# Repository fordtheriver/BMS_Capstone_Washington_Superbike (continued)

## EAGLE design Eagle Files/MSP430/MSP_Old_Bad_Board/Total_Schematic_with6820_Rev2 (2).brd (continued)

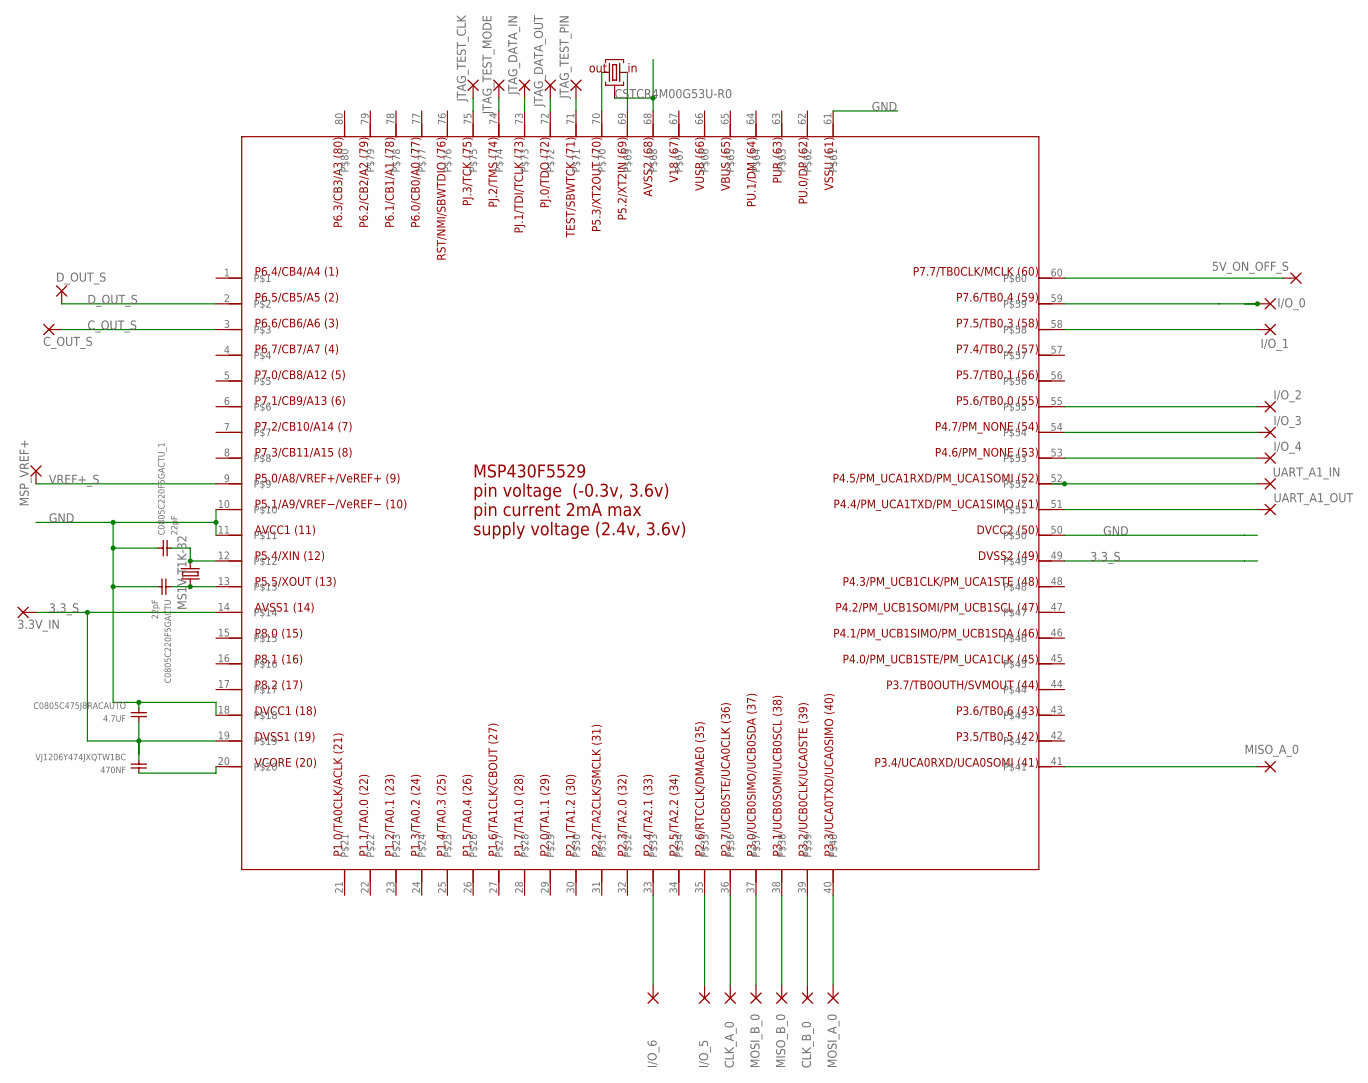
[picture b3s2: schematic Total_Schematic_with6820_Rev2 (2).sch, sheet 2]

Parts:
3.3V_IN, 5V_ON_OFF_S: 2,15/1,0
4.7UF: C0805C475J8RACAUTO
470NF: VJ1206Y474JXQTW1BC
C0805C220F5GACTU, C0805C220F5GACTU_1: 22pF; C0805C220F5GACTU
CLK_A_0: 2,15/1,0
CLK_B_0: 2,15/1,0
C_OUT_S: 2,15/1,0
D_OUT_S: 2,15/1,0
I/O_0, I/O_1, I/O_2, I/O_3, I/O_4, I/O_5, I/O_6: 2,15/1,0
JTAG_DATA_IN: 2,15/1,0
JTAG_DATA_OUT: 2,15/1,0
JTAG_TEST_CLK: 2,15/1,0
JTAG_TEST_MODE: 2,15/1,0
JTAG_TEST_PIN: 2,15/1,0
MISO_A_0: 2,15/1,0
MISO_B_0: 2,15/1,0
MOSI_A_0: 2,15/1,0
MOSI_B_0: 2,15/1,0
MSP_VREF+: 2,15/1,0
U$15: MS1V-T1K-32; MS1V-T1K
U$16: CSTCR4M00G53U-R0
U$17: MSP430F5529; QFP80-841
UART_A1_IN, UART_A1_OUT: 2,15/1,0

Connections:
3.3_S: 3.3V_IN.1, 4.7UF.2, 470NF.1, U$17.14, U$17.19, U$17.49
C_OUT_S: C_OUT_S.1, U$17.3
D_OUT_S: D_OUT_S.1, U$17.2
GND: 4.7UF.1, C0805C220F5GACTU.1, C0805C220F5GACTU_1.2, U$16.GND, U$17.10, U$17.11, U$17.18, U$17.50, U$17.61, U$17.68; also elsewhere on the board
I/O_1: I/O_0.1, U$17.59
MISO_A_0: MISO_A_0.1, U$17.41
MOSI_B_0: MOSI_B_0.1, U$17.37
unnamed: U$16.OUT, U$17.70
unnamed: U$16.IN, U$17.69
unnamed: I/O_6.1, U$17.33
unnamed: I/O_5.1, U$17.35
unnamed: 470NF.2, U$17.20
unnamed: MISO_B_0.1, U$17.38
unnamed: C0805C220F5GACTU_1.1, U$15.P$2 (1), U$17.12
unnamed: C0805C220F5GACTU.2, U$15.P$3 (2), U$17.13
unnamed: CLK_B_0.1, U$17.39
unnamed: MOSI_A_0.1, U$17.40
unnamed: U$17.51, UART_A1_OUT.1
unnamed: I/O_4.1, U$17.53
unnamed: I/O_3.1, U$17.54
unnamed: I/O_2.1, U$17.55
unnamed: I/O_1.1, U$17.58
unnamed: 5V_ON_OFF_S.1, U$17.60
unnamed: JTAG_TEST_PIN.1, U$17.71
unnamed: JTAG_DATA_OUT.1, U$17.72
unnamed: JTAG_DATA_IN.1, U$17.73
unnamed: JTAG_TEST_MODE.1, U$17.74
unnamed: JTAG_TEST_CLK.1, U$17.75
unnamed: CLK_A_0.1, U$17.36
UART_A_IN: U$17.52, UART_A1_IN.1
VREF+_S: MSP_VREF+.1, U$17.9

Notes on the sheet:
CSTCR4M00G53U-R0

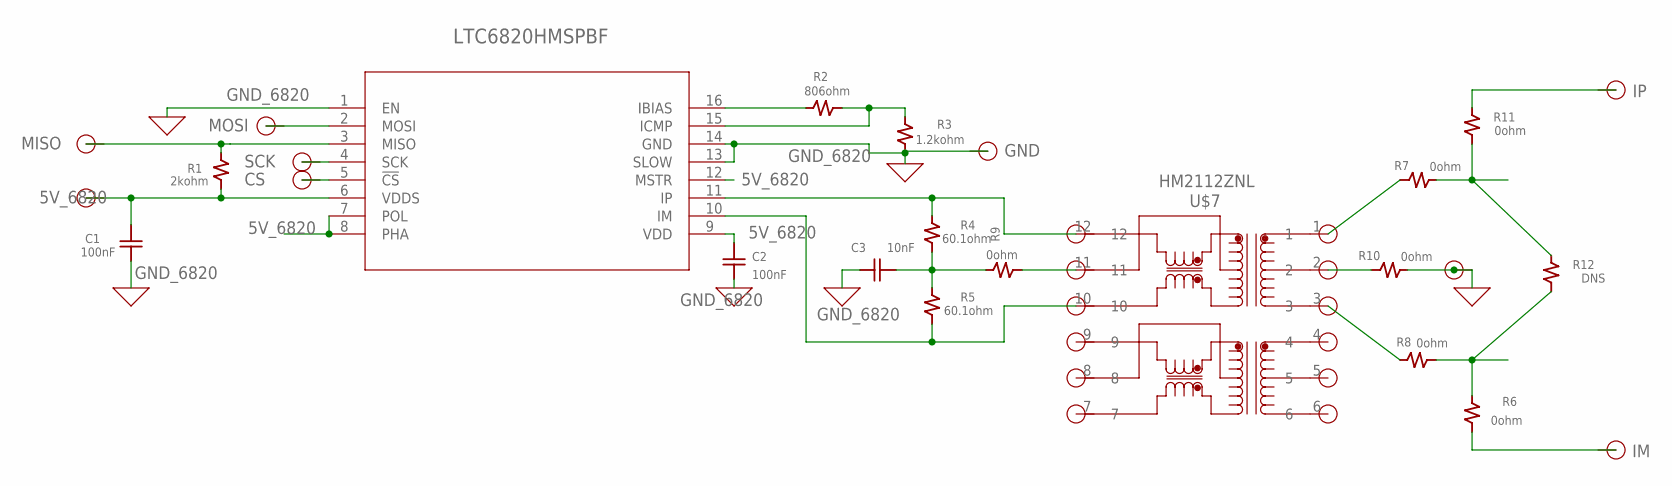
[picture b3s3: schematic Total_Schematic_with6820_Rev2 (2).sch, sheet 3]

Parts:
5V_6820: HEADER_PIN_2.15/1.0; 2,15/1,0
C1, C2: 100nF; 0805_CAPACITOR; MPN MC0805B104K160CT
C3: 10nF; 0805_CAPACITOR; MPN MC0805B104K160CT
CS: HEADER_PIN_2.15/1.0; 2,15/1,0
GND: HEADER_PIN_2.15/1.0; 2,15/1,0
GND_6820: HEADER_PIN_2.15/1.0; 2,15/1,0
IM: HEADER_PIN_2.15/1.0; 2,15/1,0
IP: HEADER_PIN_2.15/1.0; 2,15/1,0
MISO: HEADER_PIN_2.15/1.0; 2,15/1,0
MOSI: HEADER_PIN_2.15/1.0; 2,15/1,0
R1: 2kohm; 0805_RESISTOR; MPN ERJ-6ENF2001V
R2: 806ohm; 0805_RESISTOR; MPN CRCW0805806RFKEA
R3: 1.2kohm; 0805_RESISTOR; MPN MC0805S8F1201T5E
R4, R5: 60.1ohm; 0805_RESISTOR; MPN CR0805-FX-1200GLF
R6, R7, R8, R9, R10, R11: 0ohm; 0805_RESISTOR; MPN CR0805-FX-1200GLF
R12: DNS; 0805_RESISTOR; MPN CR0805-FX-1200GLF
SCK: HEADER_PIN_2.15/1.0; 2,15/1,0
U2: LTC6820HMSPBF; MSOP-16_MS
U$7: HM2112ZNL; HM2112ZNL_12SMT

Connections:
5V_6820: 5V_6820.1, C1.P$2, C2.P$2, R1.P$2, U2.6 (VDDS), U2.7 (POL), U2.8 (PHA), U2.9 (VDD), U2.12 (MSTR)
CS: CS.1, U2.5 (!CS)
GND_6820: C1.P$1, C2.P$1, C3.P$1, GND.1, GND_6820.1, R3.P$2, R10.P$1, U2.1 (EN), U2.13 (SLOW), U2.14 (GND)
IBIAS: R2.P$1, U2.16 (IBIAS)
ICMP: R2.P$2, R3.P$1, U2.15 (ICMP)
IM: R5.P$2, U2.10 (IM), U$7.10
IP: R4.P$1, U2.11 (IP), U$7.12
MISO: MISO.1, R1.P$1, U2.3 (MISO)
MOSI: MOSI.1, U2.2 (MOSI)
unnamed: R8.P$1, U$7.3
unnamed: C3.P$2, R4.P$2, R5.P$1, R9.P$1
unnamed: R7.P$2, U$7.1
unnamed: R9.P$2, U$7.11
unnamed: R10.P$2, U$7.2
unnamed: R6.P$1, R8.P$2, R12.P$2
unnamed: R7.P$1, R11.P$2, R12.P$1
unnamed: IP.1, R11.P$1
unnamed: IM.1, R6.P$2
SCK: SCK.1, U2.4 (SCK)

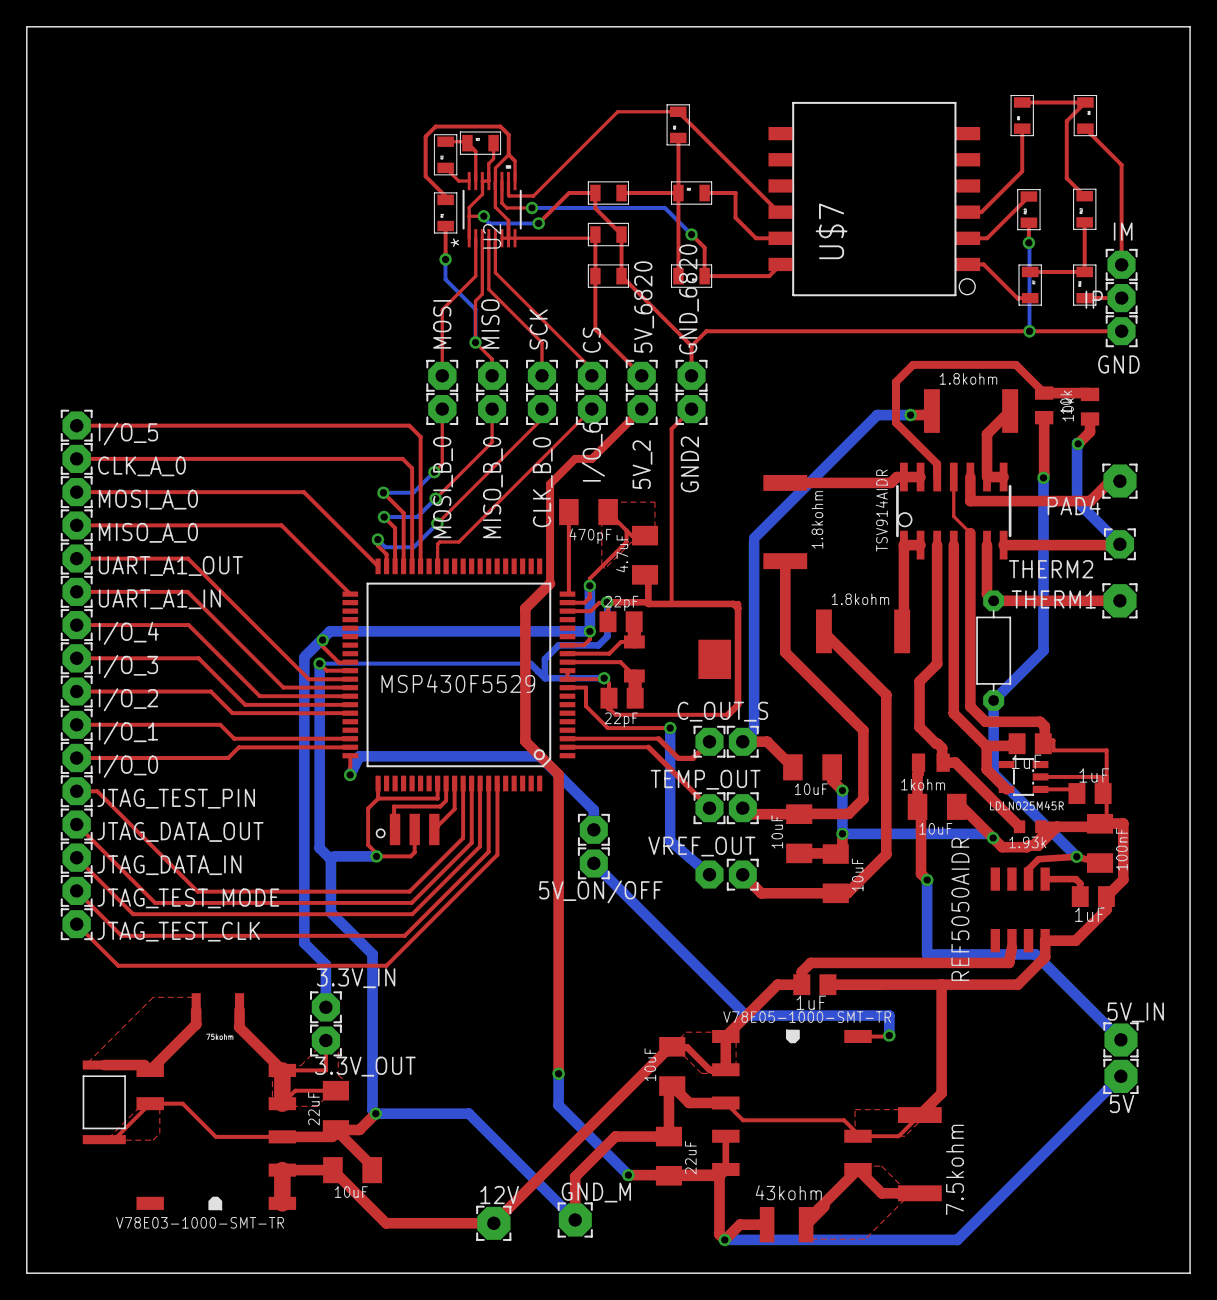
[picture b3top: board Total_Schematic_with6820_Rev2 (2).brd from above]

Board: 2 copper layers, 88.9 x 95.2 mm, 102 parts (1 on the bottom side), 72 nets.

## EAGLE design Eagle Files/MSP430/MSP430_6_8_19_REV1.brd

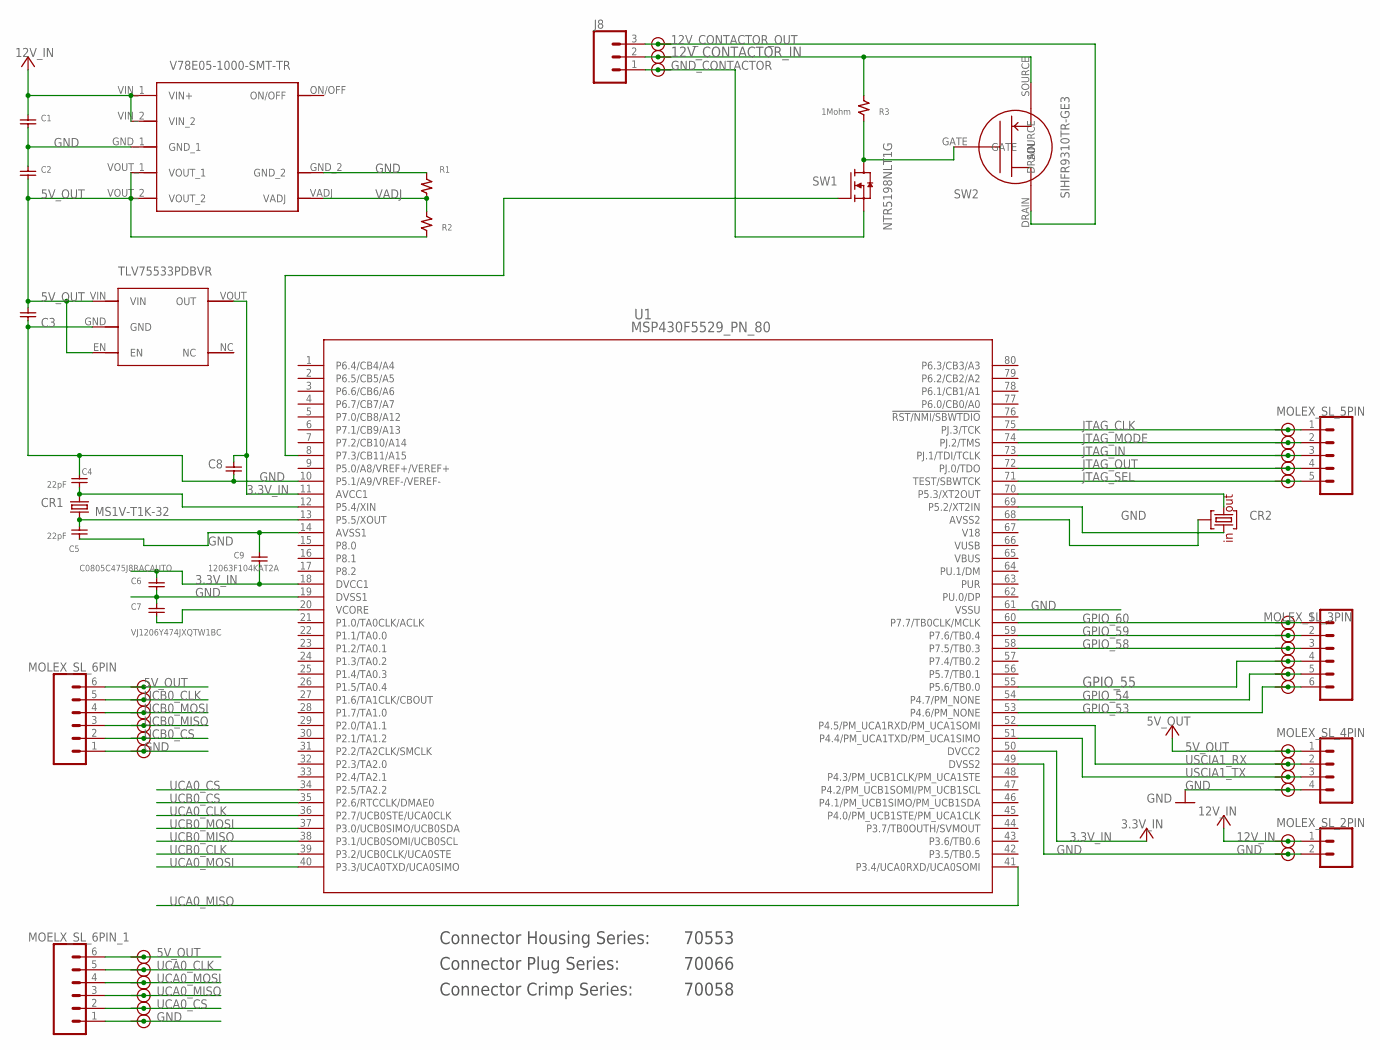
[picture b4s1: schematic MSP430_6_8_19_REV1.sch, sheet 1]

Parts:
C1: CGA5L1X7R1H106K160AC
C2: C1206C226K8RACTU
C3, C8: C0805C105J4RECTU
C4, C5: 22pF; C0805C220F5GACTU
C6: C0805C475J8RACAUTO
C7: VJ1206Y474JXQTW1BC
C9: 12063F104KAT2A
CR1: MS1V-T1K-32; MS1V-T1K
CR2: CSTCR4M00G53U-R0
J8: CONN_03; 1X03
MOELX_SL_6PIN_1: CONN_06SILK_FEMALE_PTH; 1X06
MOLEX_SL_2PIN: CONN_02; 1X02
MOLEX_SL_3PIN, MOLEX_SL_6PIN: CONN_06SILK_FEMALE_PTH; 1X06
MOLEX_SL_4PIN: CONN_04; 1X04
MOLEX_SL_5PIN: CONN_05; 1X05
PS1: V78E05-SMT-TR; V78E05-1000-SMT-TR
PS2: TLV75533PDBVR
R1: RC2512FK-077K5L
R2: CRCW121043K0FKEAHP
R3: 1Mohm; THROUGHHOLERESISTOR
SW1: NTR5198NLT1G
SW2: PMOS; SIHFR9310TR-GE3
U1: MSP430F5529_PN_80; PN80
U$10, U$11, U$12, U$13, U$14, U$15, U$16, U$17, U$18, U$19, U$20, U$21, U$22, U$23, U$24, U$25, U$26, U$27, U$28, U$29, U$30, U$31, U$32, U$33, U$34, U$35, U$36, U$37, U$38, U$39, U$40, U$41: HEADER_PIN_2.15/1.0; 2,15/1,0

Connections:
3.3V_IN: C6.2, C8.2, C9.1, PS2.VOUT (OUT), U1.11 (AVCC1), U1.18 (DVCC1), U1.50 (DVCC2)
5V_OUT: C2.1, C3.2, MOELX_SL_6PIN_1.6, MOLEX_SL_4PIN.1, MOLEX_SL_6PIN.6, PS1.VOUT_1, PS1.VOUT_2, PS2.EN, PS2.VIN, R2.2, U$11.1, U$17.1, U$27.1; also elsewhere on the board
12V_CONTACTOR_IN: J8.2, R3.1, SW2.SOURCE, U$40.1
12V_CONTACTOR_OUT: J8.3, SW2.DRAIN, U$39.1
12V_IN: C1.2, MOLEX_SL_2PIN.1, PS1.VIN_1 (VIN+), PS1.VIN_2, U$23.1
GND: C1.1, C2.2, C3.1, C4.1, C5.2, C6.1, C7.2, C8.1, C9.2, CR2.GND, MOELX_SL_6PIN_1.1, MOLEX_SL_2PIN.2, MOLEX_SL_4PIN.4, MOLEX_SL_6PIN.1, PS1.GND_1, PS1.GND_2, PS2.GND, R1.2, U1.10 (P5.1/A9/VREF-/VEREF-), U1.14 (AVSS1), U1.19 (DVSS1), U1.49 (DVSS2), U1.61 (VSSU), U1.68 (AVSS2), U$10.1, U$16.1, U$22.1, U$24.1; also elsewhere on the board
GND_CONTACTOR: J8.1, SW1.SOURCE, U$41.1
GPIO_53: MOLEX_SL_3PIN.6, U1.53 (P4.6/PM_NONE), U$28.1
GPIO_54: MOLEX_SL_3PIN.5, U1.54 (P4.7/PM_NONE), U$29.1
GPIO_55: MOLEX_SL_3PIN.4, U1.55 (P5.6/TB0.0), U$30.1
GPIO_58: MOLEX_SL_3PIN.3, U1.58 (P7.5/TB0.3), U$31.1
GPIO_59: MOLEX_SL_3PIN.2, U1.59 (P7.6/TB0.4), U$32.1
GPIO_60: MOLEX_SL_3PIN.1, U1.60 (P7.7/TB0CLK/MCLK), U$33.1
JTAG_CLK: MOLEX_SL_5PIN.1, U1.75 (PJ.3/TCK), U$38.1
JTAG_IN: MOLEX_SL_5PIN.3, U1.73 (PJ.1/TDI/TCLK), U$36.1
JTAG_MODE: MOLEX_SL_5PIN.2, U1.74 (PJ.2/TMS), U$37.1
JTAG_OUT: MOLEX_SL_5PIN.4, U1.72 (PJ.0/TDO), U$35.1
JTAG_SEL: MOLEX_SL_5PIN.5, U1.71 (TEST/SBWTCK), U$34.1
unnamed: C7.1, U1.20 (VCORE)
unnamed: CR2.IN, U1.69 (P5.2/XT2IN)
unnamed: CR2.OUT, U1.70 (P5.3/XT2OUT)
unnamed: C4.2, CR1.P$2 (1), U1.12 (P5.4/XIN)
unnamed: C5.1, CR1.P$3 (2), U1.13 (P5.5/XOUT)
unnamed: R3.2, SW1.DRAIN, SW2.GATE
unnamed: SW1.GATE, U1.8 (P7.3/CB11/A15)
UCA0_CLK: MOELX_SL_6PIN_1.5, U1.36 (P2.7/UCB0STE/UCA0CLK), U$18.1
UCA0_CS: MOELX_SL_6PIN_1.2, U1.34 (P2.5/TA2.2), U$21.1
UCA0_MISO: MOELX_SL_6PIN_1.3, U1.41 (P3.4/UCA0RXD/UCA0SOMI), U$20.1
UCA0_MOSI: MOELX_SL_6PIN_1.4, U1.40 (P3.3/UCA0TXD/UCA0SIMO), U$19.1
UCB0_CLK: MOLEX_SL_6PIN.5, U1.39 (P3.2/UCB0CLK/UCA0STE), U$12.1; also elsewhere on the board
UCB0_CS: MOLEX_SL_6PIN.2, U1.35 (P2.6/RTCCLK/DMAE0), U$15.1; also elsewhere on the board
UCB0_MISO: MOLEX_SL_6PIN.3, U1.38 (P3.1/UCB0SOMI/UCB0SCL), U$14.1; also elsewhere on the board
UCB0_MOSI: MOLEX_SL_6PIN.4, U1.37 (P3.0/UCB0SIMO/UCB0SDA), U$13.1; also elsewhere on the board
USCIA1_RX: MOLEX_SL_4PIN.2, U1.52 (P4.5/PM_UCA1RXD/PM_UCA1SOMI), U$26.1
USCIA1_TX: MOLEX_SL_4PIN.3, U1.51 (P4.4/PM_UCA1TXD/PM_UCA1SIMO), U$25.1
V18: U1.67 (V18)
VADJ: PS1.VADJ, R1.1, R2.1
VBUS: U1.65 (VBUS)
VUSB: U1.66 (VUSB)

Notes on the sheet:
Connector Housing Series:
Connector Plug Series:
Connector Crimp Series:
70553
70066
70058
SW1
SW2
CR2
CR1

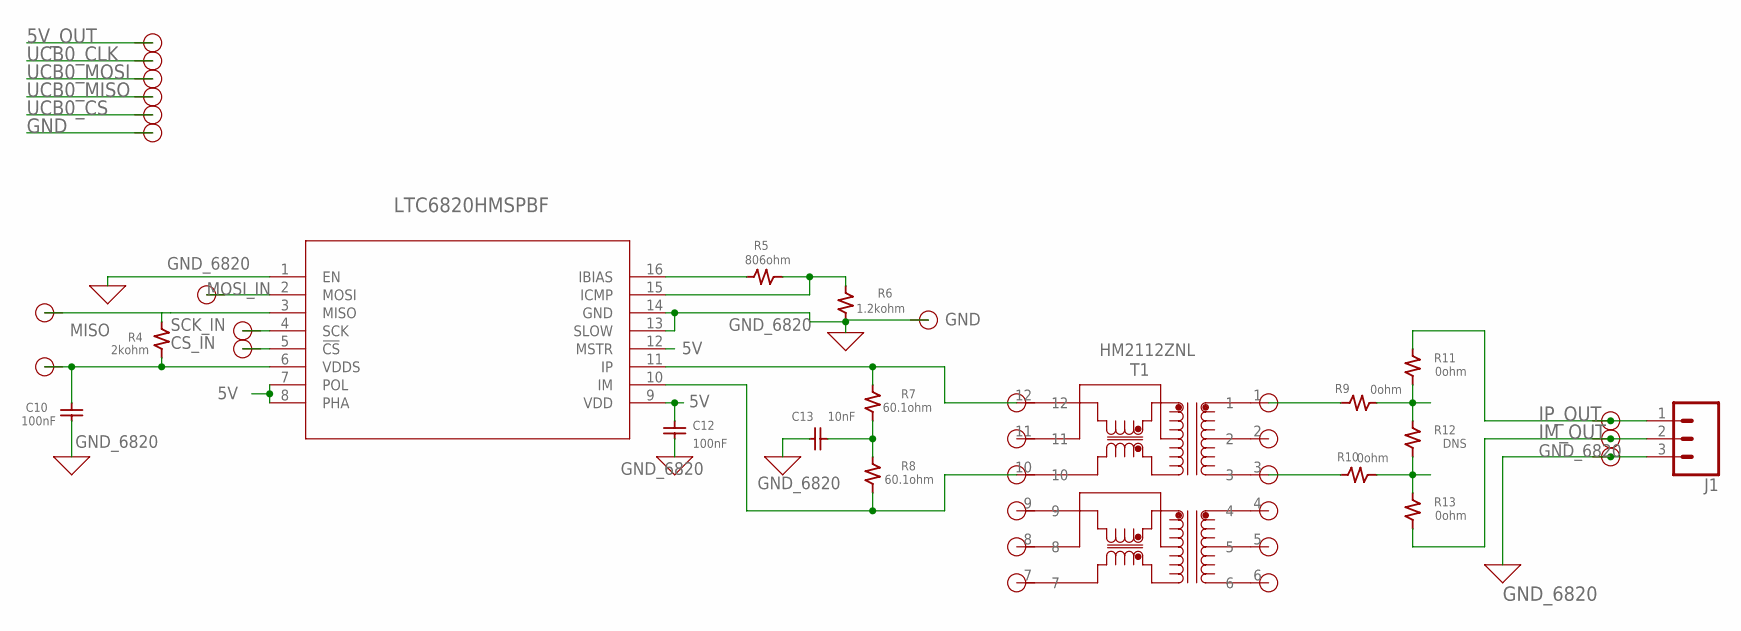
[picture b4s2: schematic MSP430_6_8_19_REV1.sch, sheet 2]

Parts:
+5V: HEADER_PIN_2.15/1.0; 2,15/1,0
C10, C12: 100nF; 0805_CAPACITOR; MPN MC0805B104K160CT
C13: 10nF; 0805_CAPACITOR; MPN MC0805B104K160CT
CS: HEADER_PIN_2.15/1.0; 2,15/1,0
GND: HEADER_PIN_2.15/1.0; 2,15/1,0
J1: CONN_03; 1X03
MISO: HEADER_PIN_2.15/1.0; 2,15/1,0
MOSI: HEADER_PIN_2.15/1.0; 2,15/1,0
R4: 2kohm; 0805_RESISTOR; MPN ERJ-6ENF2001V
R5: 806ohm; 0805_RESISTOR; MPN CRCW0805806RFKEA
R6: 1.2kohm; 0805_RESISTOR; MPN MC0805S8F1201T5E
R7, R8: 60.1ohm; 0805_RESISTOR; MPN CR0805-FX-1200GLF
R9, R10, R11, R13: 0ohm; 0805_RESISTOR; MPN CR0805-FX-1200GLF
R12: DNS; 0805_RESISTOR; MPN CR0805-FX-1200GLF
SCK: HEADER_PIN_2.15/1.0; 2,15/1,0
T1: HM2112ZNL; HM2112ZNL_12SMT
U2: LTC6820HMSPBF; MSOP-16_MS
U$42, U$43, U$44, U$45, U$46, U$47, U$48, U$49, U$50: HEADER_PIN_2.15/1.0; 2,15/1,0

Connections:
5V: +5V.1, C10.P$2, C12.P$2, R4.P$2, U2.6 (VDDS), U2.7 (POL), U2.8 (PHA), U2.9 (VDD), U2.12 (MSTR)
5V_OUT: U$45.1; also elsewhere on the board
CS_IN: CS.1, U2.5 (!CS)
GND: U$50.1; also elsewhere on the board
GND_6820: C10.P$1, C12.P$1, C13.P$1, GND.1, J1.3, R6.P$2, U2.1 (EN), U2.13 (SLOW), U2.14 (GND), U$44.1
IBIAS: R5.P$1, U2.16 (IBIAS)
ICMP: R5.P$2, R6.P$1, U2.15 (ICMP)
IM: R8.P$2, T1.10, U2.10 (IM)
IM_OUT: J1.2, R13.P$2, U$43.1
IP: R7.P$1, T1.12, U2.11 (IP)
IP_OUT: J1.1, R11.P$1, U$42.1
MISO_IN: MISO.1, R4.P$1, U2.3 (MISO)
MOSI_IN: MOSI.1, U2.2 (MOSI)
unnamed: C13.P$2, R7.P$2, R8.P$1
unnamed: R10.P$1, T1.3
unnamed: R9.P$2, T1.1
unnamed: R10.P$2, R12.P$2, R13.P$1
unnamed: R9.P$1, R11.P$2, R12.P$1
SCK_IN: SCK.1, U2.4 (SCK)
UCB0_CLK: U$46.1; also elsewhere on the board
UCB0_CS: U$49.1; also elsewhere on the board
UCB0_MISO: U$48.1; also elsewhere on the board
UCB0_MOSI: U$47.1; also elsewhere on the board

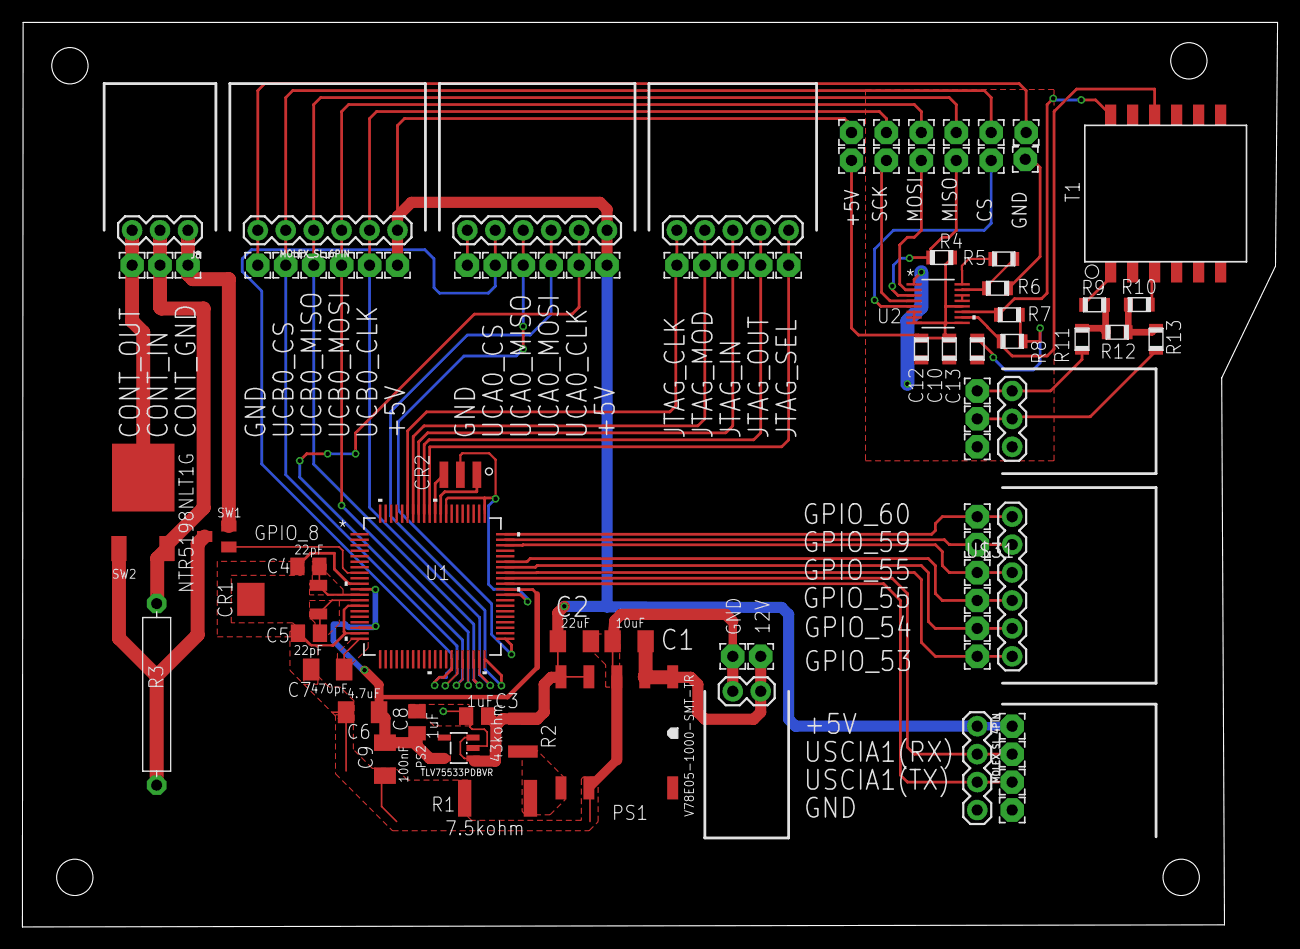
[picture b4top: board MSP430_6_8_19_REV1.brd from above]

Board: 2 copper layers, 114.1 x 82.2 mm, 89 parts (0 on the bottom side), 53 nets.

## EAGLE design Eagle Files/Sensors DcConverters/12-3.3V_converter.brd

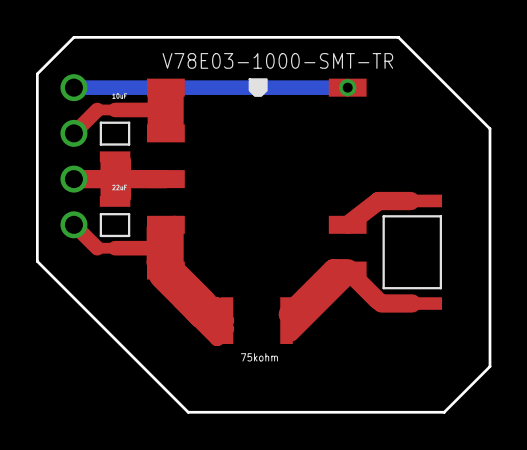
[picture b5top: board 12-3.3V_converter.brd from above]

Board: 2 copper layers, 25.1 x 20.8 mm, 5 parts (0 on the bottom side), 5 nets.

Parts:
E$1: V78E03-1000-SMT-TR
E$2: ESR25JZPF7502
E$3: CRGP2512F22K
E$4: GRT31CR61H106KE01L
E$5: GRT31CC81C226KE01L

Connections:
S$1: E$1.VIN_1, E$1.VIN_2, E$4.P$2
S$3: E$1.VOUT_1, E$1.VOUT_2, E$2.P$2, E$5.P$1
S$4: E$1.VADJ, E$2.P$1, E$3.P$2
S$5: E$1.GND_1, E$3.P$1
S$6: E$1.GND_2, E$4.P$1, E$5.P$2

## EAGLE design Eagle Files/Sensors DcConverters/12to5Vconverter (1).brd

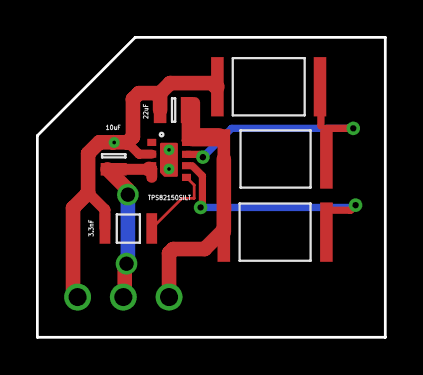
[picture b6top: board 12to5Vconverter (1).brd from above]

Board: 2 copper layers, 19.3 x 16.7 mm, 7 parts (0 on the bottom side), 6 nets.

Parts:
E$4: GRT21BR61E226ME13L
E$5: RC2512FK-07100KL
E$8: RC2512FK-07249KL
E$9: RC2512FK-0747KL
E$10: C1206C332K1RECAUTO
E$11: CC0805KFX5R8BB106
E$12: TPS82150SILT

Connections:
S$2: E$11.P$1, E$12.EN, E$12.VIN
S$3: E$5.P$1, E$12.PG
S$5: E$4.P$1, E$5.P$2, E$8.P$2, E$12.VOUT2
S$6: E$8.P$1, E$9.P$1, E$12.FB
S$8: E$4.P$2, E$9.P$2, E$10.P$2, E$11.P$2, E$12.GND
S$10: E$10.P$1, E$12.SS/TR

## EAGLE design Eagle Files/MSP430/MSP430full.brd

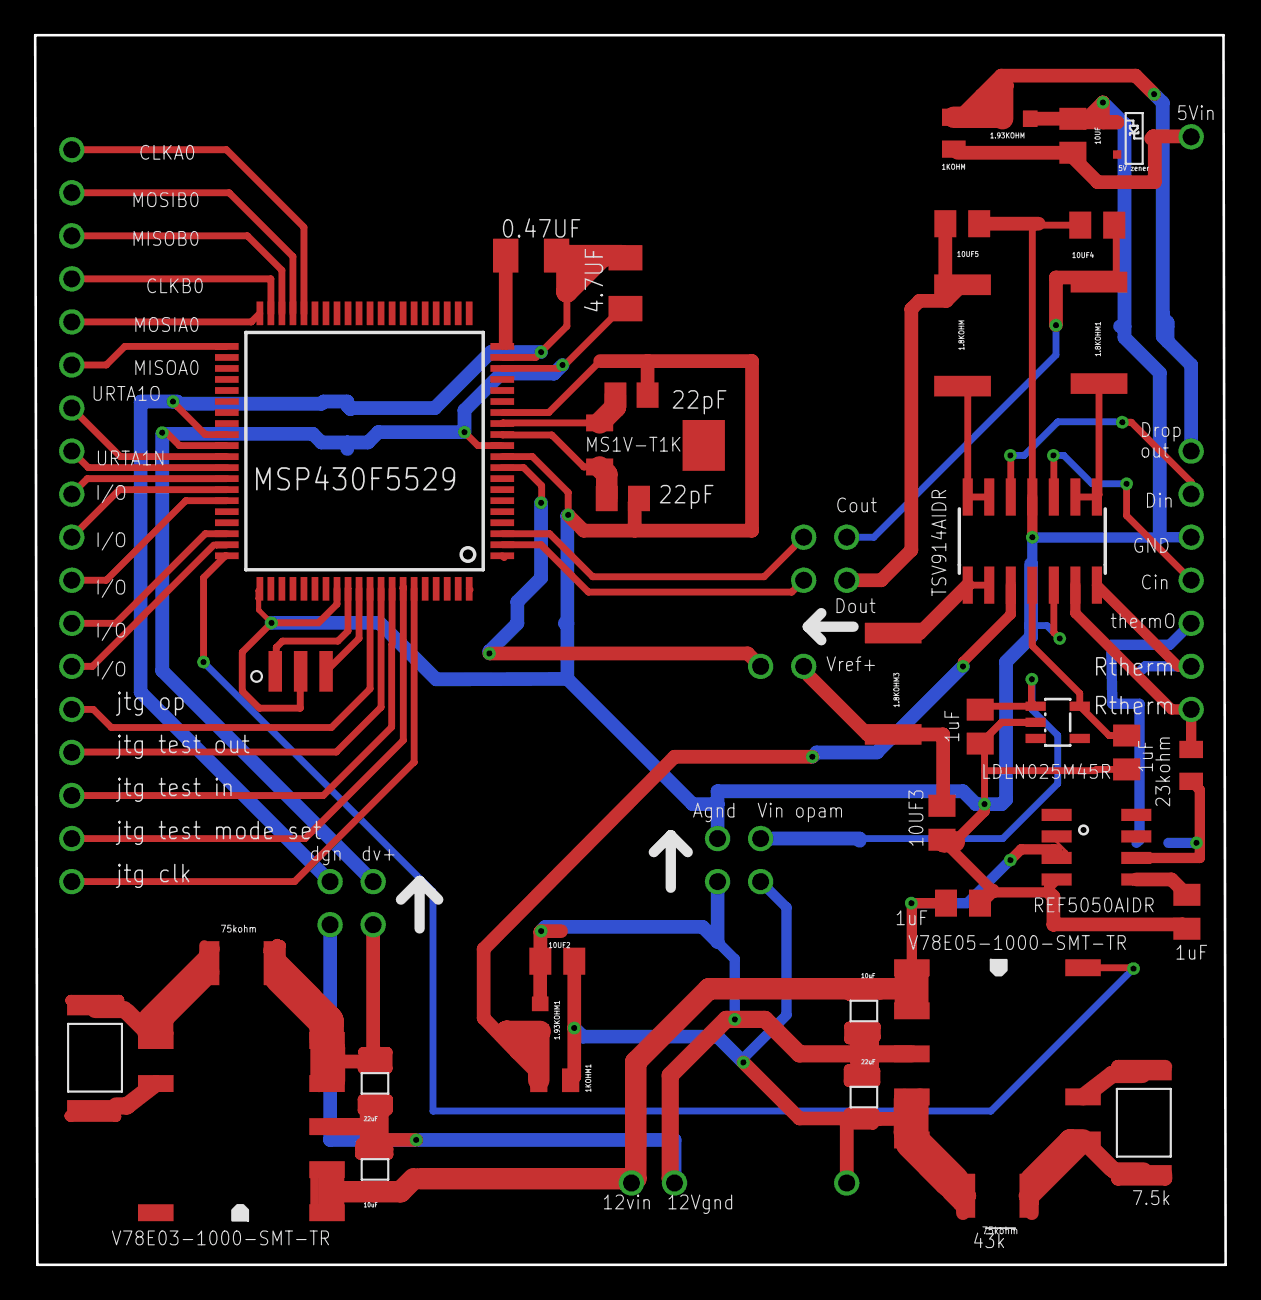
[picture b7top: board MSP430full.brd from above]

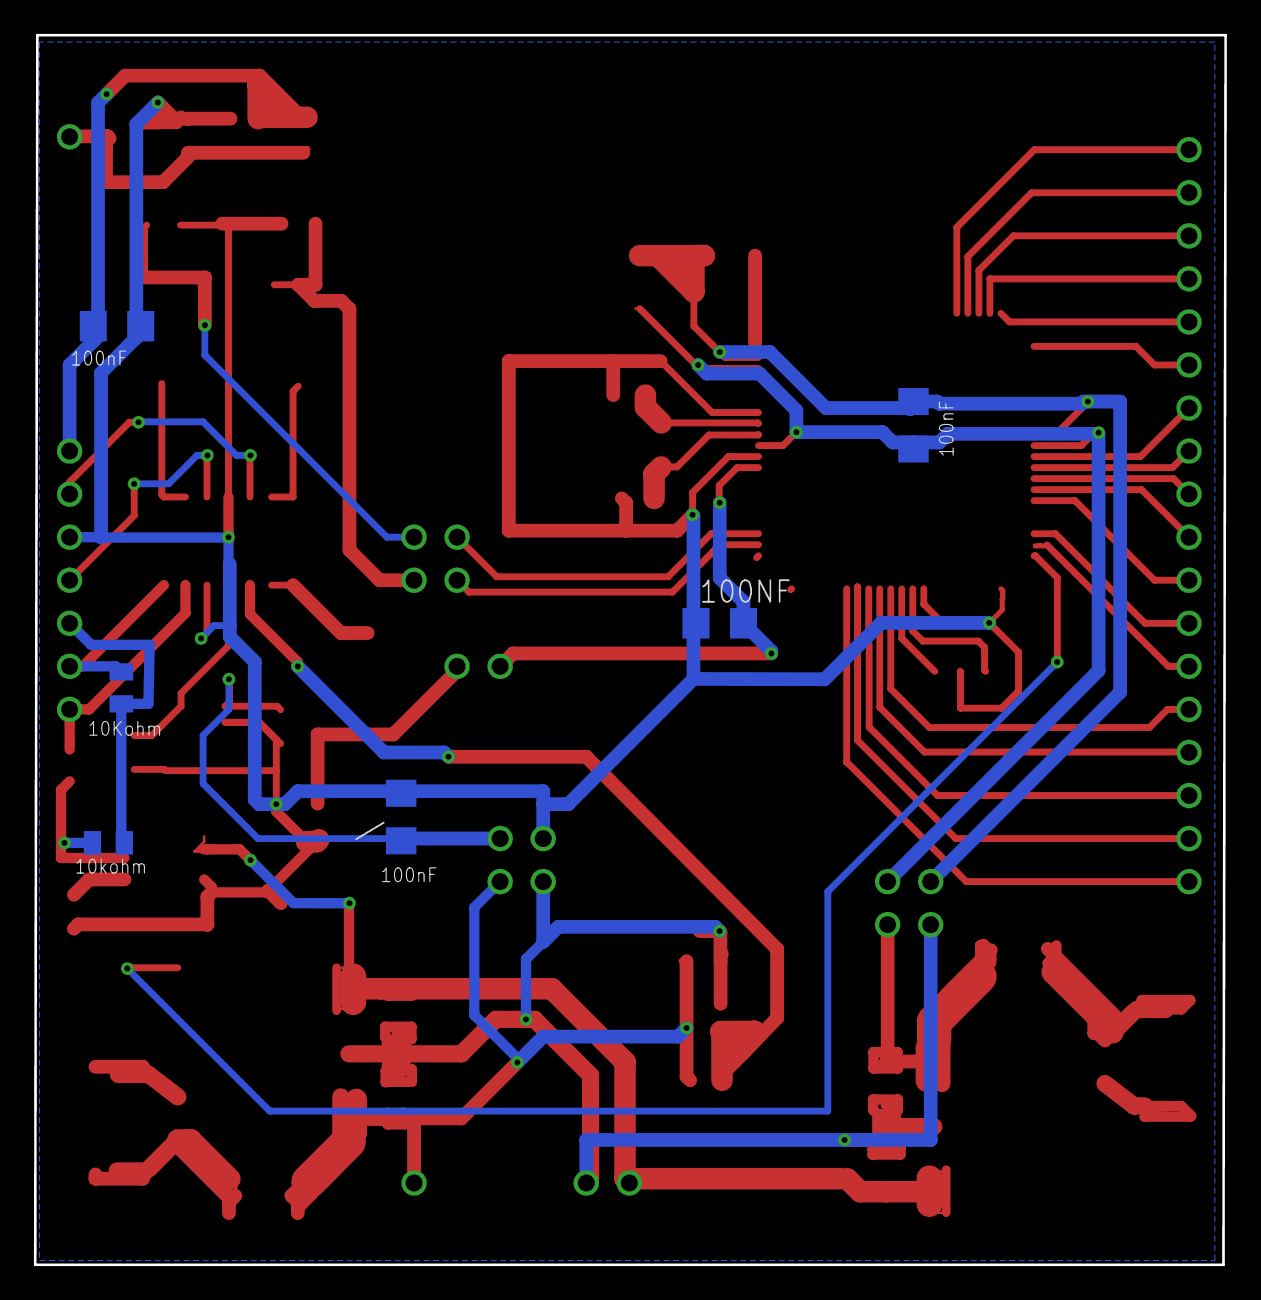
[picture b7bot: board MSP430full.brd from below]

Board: 2 copper layers, 70.2 x 72.5 mm, 44 parts (6 on the bottom side), 32 nets.

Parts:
0.47UF, 4.7UF: C1206K
1.8KOHM, 1.8KOHM1, 1.8KOHM3: R2512
1.93KOHM, 1.93KOHM1: R0603
1KOHM, 1KOHM1, 10K: R0805
10UF, 10UF2, 10UF3, 10UF4, 10UF5: C0805K
100NF: C1206
E$1: PLVA650A,215
E$2, E$8: ESR25JZPF7502
E$3, E$9: CRGP2512F22K
E$4, E$10: GRT31CR61H106KE01L
E$5, E$11: GRT31CC81C226KE01L
E$6: V78E05-1000-SMT-TR
E$7: V78E03-1000-SMT-TR
E$12: MS1V-T1K
E$13, E$15: C0805
E$14: CSTCR4M00G53U-R0
E$16: LDLN025M45R (LDO); SOT23-5
E$17, E$19: C1206
E$18, E$20: R0805
E$21, E$22, E$24, E$25: 1uF; C0805K
E$23: SO08
MSP430F5529: QFP80_SOT496-1
TSV914AIDR: SO14
\: C1206

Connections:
3.3V: 4.7UF.1, E$7.VOUT_1, E$7.VOUT_2, E$8.P$2, E$11.P$1, E$17.1, MSP430F5529.11, MSP430F5529.18, MSP430F5529.50
3.3VREF: 100NF.2, MSP430F5529.9
5V: 1KOHM1.2, 10UF2.2, E$2.P$2, E$5.P$1, E$6.VOUT_1, E$6.VOUT_2
5V.: E$16.1, E$16.3, E$21.2, \.1
5VREF: 1.93KOHM1.2, 1KOHM1.1, TSV914AIDR.3
5V_ON/OFF: E$6.ON/OFF, MSP430F5529.60
12VIN: E$4.P$2, E$6.VIN_1, E$6.VIN_2, E$7.VIN_1, E$7.VIN_2, E$10.P$2, E$23.2, E$25.2
ANG_GND: 1.93KOHM.1, 10UF.1, 10UF3.1, 10UF4.1, 10UF5.1, 100NF.1, E$1.1, E$13.2, E$14.GND, E$15.2, E$16.2, E$19.2, E$21.1, E$22.1, E$23.4, E$24.1, E$25.1, MSP430F5529.10, MSP430F5529.14, MSP430F5529.61, MSP430F5529.68, TSV914AIDR.5, TSV914AIDR.11, \.2
DGT_GND: 0.47UF.2, 4.7UF.2, E$17.2, MSP430F5529.19, MSP430F5529.49
GND: 1.93KOHM1.1, 10UF2.1, E$4.P$1, E$5.P$2, E$6.GND_2, E$7.GND_2, E$10.P$1, E$11.P$2
S$1: 1.8KOHM.2, TSV914AIDR.13, TSV914AIDR.14
S$2: 1.8KOHM1.2, TSV914AIDR.8, TSV914AIDR.9
S$3: 1.8KOHM.1, 10UF5.2
S$8: E$14.IN, MSP430F5529.69
S$9: 1.8KOHM3.1, TSV914AIDR.1, TSV914AIDR.2
S$11: 1.8KOHM3.2, 10UF3.2
S$13: 10K.2, TSV914AIDR.7
S$14: E$16.5, E$22.2, TSV914AIDR.4
S$16: E$14.OUT, MSP430F5529.70
S$17: 1.93KOHM.2, 1KOHM.1, E$19.1
S$19: E$7.VADJ, E$9.P$2
S$20: 1KOHM.2, 10UF.2, E$1.3
S$24: E$2.P$1, E$3.P$2, E$6.VADJ
S$25: E$3.P$1, E$6.GND_1
S$29: E$7.GND_1, E$9.P$1
S$31: E$18.2, TSV914AIDR.6
S$32: E$18.1, E$20.2, E$23.6
S$38: 0.47UF.1, MSP430F5529.20
S$39: 10K.1, E$20.1
S$58: E$12.P$3, E$13.1, MSP430F5529.13
S$59: E$12.P$2, E$15.1, MSP430F5529.12
S$61: E$23.5, E$24.2

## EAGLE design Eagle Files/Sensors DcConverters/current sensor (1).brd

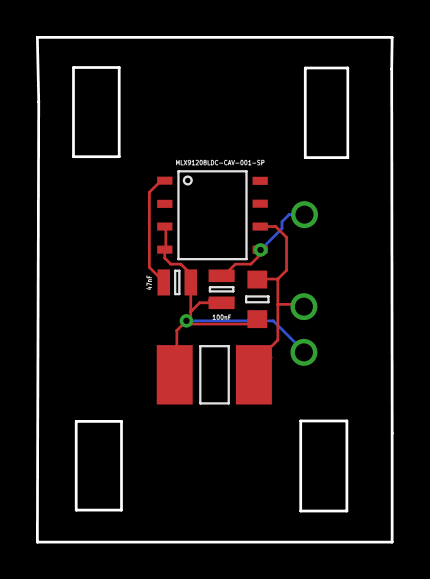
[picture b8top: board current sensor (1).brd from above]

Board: 2 copper layers, 19.7 x 28.0 mm, 5 parts (0 on the bottom side), 4 nets.

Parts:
E$1: MLX91208LDC-CAV-001-SP
E$2: AS0805KKX7R9BB104
E$3: GRM2195C1H103FA01D
E$6: C0805C473K8RACTU
E$8: 352220KFT

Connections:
S$1: E$1.TEST, E$1.VSS, E$2.P$2, E$3.P$2, E$6.P$1, E$8.P$2
S$2: E$1.VDEC, E$6.P$2
S$3: E$1.VDD, E$2.P$1
S$4: E$1.OUT, E$3.P$1, E$8.P$1

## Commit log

2019-04-12 Commited Bryan's CCS Workspace
2019-04-12 commit message
2019-04-12 Committing work from Friday morning
2019-04-14 adding work from 4/14/19
2019-04-14 Added work from afternoon of 4/14/19
2019-04-15 Added work from morning of 4/15/19
2019-04-15 Work from mid morning of 4/15/19
2019-04-17 added work from evening of 4_16_19
2019-04-19 Work from morning 4/19/19
2019-04-19 Added files from 4/19/19
2019-05-02 Adding work from 5/1
2019-05-12 Adding work from 5_12
2019-05-27 work from 5/26
2019-05-29 Minor chanes
2019-05-29 Removed Gitignore
    trying to fix nathan
2019-05-29 Updating Repository
    updating
2019-05-29 Deleted old CCS Workspaces
    n/a
2019-06-06 Commiting files from 6/4/19
    Worked on bug where the cells don't balance properly
2019-06-07 Restructure Data Structures and Hierarchy
    Modified data structures. GPIO conversion still doesn't work, but everything else does.
2019-06-07 Got GPIO Readings to Work
    This program works. Next step is to implement a lookup table to extract temp values
2019-06-08 Attempted to fix daisy chain balancing - did not
2019-06-13 Added EAGLE PCB Files
    Added files from Google Drive to git repo for reference in Capstone report
2019-06-13 Updated ReadMe
    Added a better description of the project.
